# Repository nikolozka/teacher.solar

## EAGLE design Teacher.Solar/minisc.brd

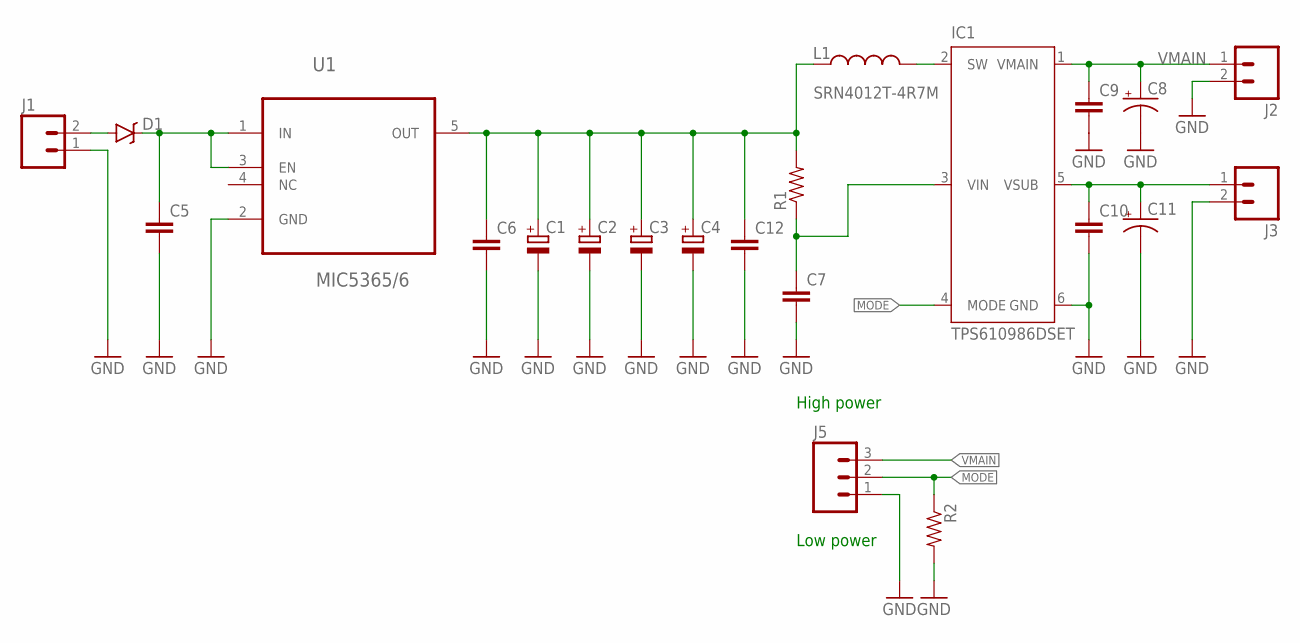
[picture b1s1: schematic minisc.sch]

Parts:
C1, C2, C3, C4: CPOL-EUE3.5-8; E3,5-8
C5, C6, C7, C9, C10, C12: CAP0805; 0805
C8, C11: CAP_POL3528-KIT; EIA3528-KIT
D1: DIODE-SCHOTTKY-BAT20J; SOD-323
IC1: TPS610986DSET; WSON-6
J1, J2, J3: M02PTH; 1X02
J5: M03PTH; 1X03
L1: SRN4012T-4R7M; CR54
R1, R2: RESISTOR0805-RES; 0805
U1: MIC5365/6; SC-70-5

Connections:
GND: C1.-, C2.-, C3.-, C4.-, C5.2, C6.2, C7.2, C8.C (-), C9.2, C10.2, C11.C (-), C12.2, IC1.6 (GND), J1.1, J2.2, J3.2, J5.1, R2.2, U1.2 (GND)
MODE: IC1.4 (MODE), J5.2, R2.1
unnamed: C5.1, D1.C, U1.1 (IN), U1.3 (EN)
unnamed: C1.+, C2.+, C3.+, C4.+, C6.1, C12.1, L1.P$1 (1), R1.2, U1.5 (OUT)
unnamed: IC1.2 (SW), L1.P$2 (2)
unnamed: C7.1, IC1.3 (VIN), R1.1
unnamed: C10.1, C11.A (+), IC1.5 (VSUB), J3.1
unnamed: D1.A, J1.2
VMAIN: C8.A (+), C9.1, IC1.1 (VMAIN), J2.1, J5.3

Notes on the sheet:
High power
Low power

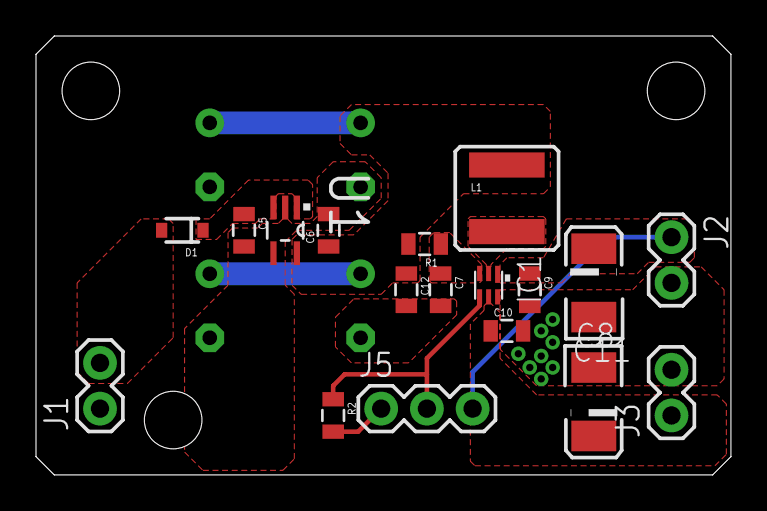
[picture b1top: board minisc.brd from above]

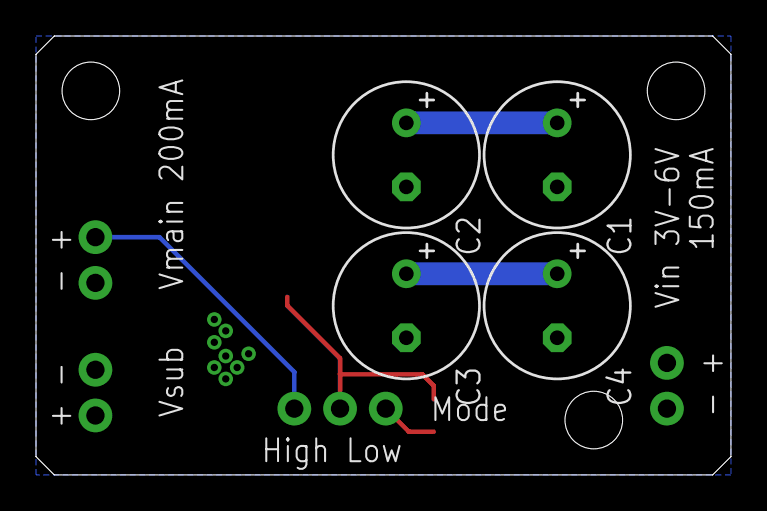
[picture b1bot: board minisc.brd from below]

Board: 2 copper layers, 38.6 x 24.4 mm, 22 parts (4 on the bottom side), 9 nets.

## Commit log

2023-11-09 restructured directory, added all relevant files

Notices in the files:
parts and their libraries:
SparkFun-Passives: Licensing: Creative Commons ShareAlike 4.0 International - https://creativecommons.org/licenses/by-sa/4.0
